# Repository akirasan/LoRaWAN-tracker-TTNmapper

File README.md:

# LoRaWAN-tracker-TTNmapper
Tracker basado en Arduino Mini Pro + GPS + RFM95W (LoRa)
Podéis encontrar toda la info del proyecto en http://akirasan.net/nodo-de-mapeo-ttnmapper-arduino-gps-lorawan

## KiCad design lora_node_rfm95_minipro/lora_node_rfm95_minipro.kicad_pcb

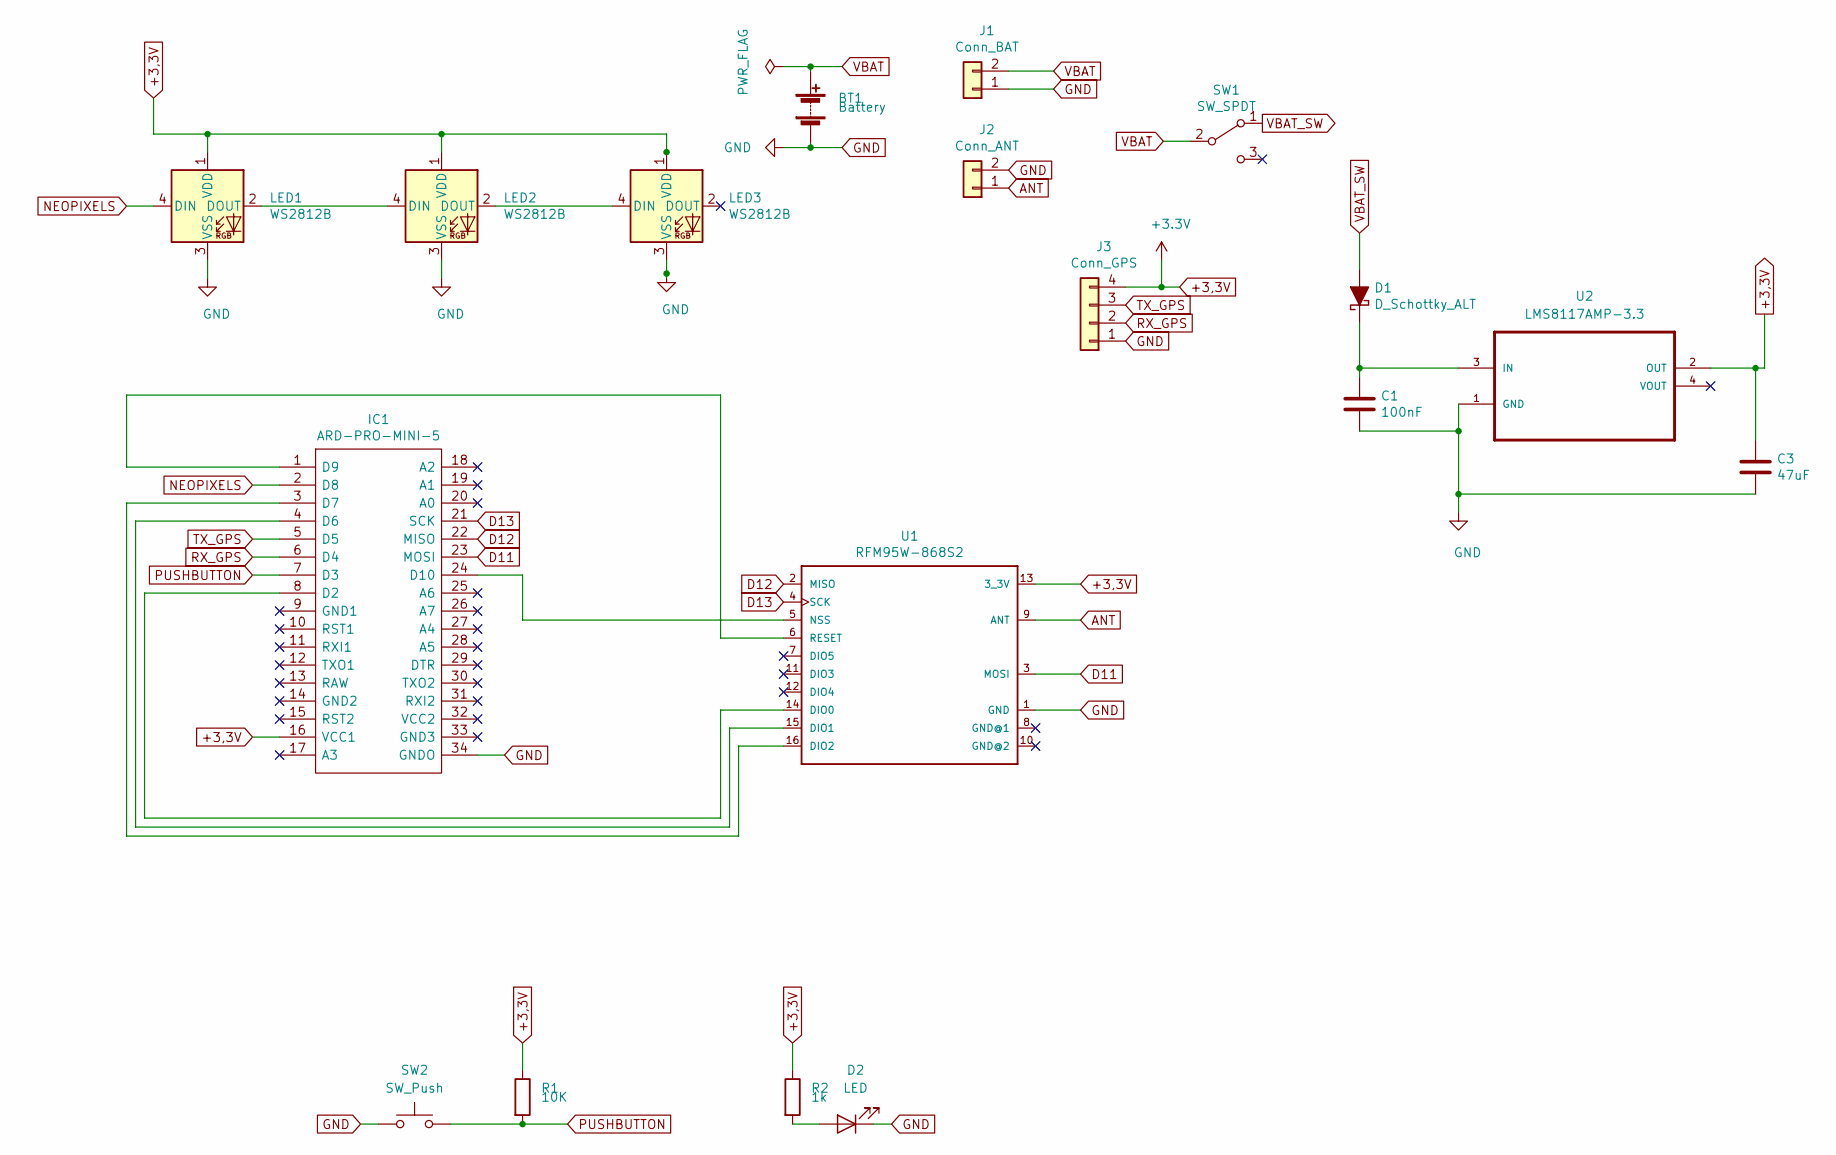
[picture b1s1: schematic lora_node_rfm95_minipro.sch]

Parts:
BT1: Battery
C1: 100nF; C_0805_2012Metric_Pad1.29x1.40mm_HandSolder
C3: 47uF; C_0805_2012Metric_Pad1.29x1.40mm_HandSolder
D1: D_Schottky_ALT; D_1206_3216Metric_Pad1.22x1.80mm_HandSolder
D2: LED; D_0805_2012Metric_Pad1.12x1.40mm_HandSolder
IC1: ARD-PRO-MINI-5; ARDPROMINI5_SMD; Mouser Part Number 992-ARD-PRO-MINI-5
J1: Conn_BAT; JST_PH_B2B-PH-SM4-TB_1x02-1MP_P2.00mm_Vertical
J2: Conn_ANT; SMA_Molex_73251-1153_EdgeMount_Horizontal
J3: Conn_GPS; GPS_module_SMD
LED1, LED2, LED3: WS2812B; LED_WS2812B_PLCC4_5.0x5.0mm_P3.2mm
R1: 10K; R_0805_2012Metric_Pad1.29x1.40mm_HandSolder
R2: 1k; R_0805_2012Metric_Pad1.29x1.40mm_HandSolder
SW1: SW_SPDT; SW_SPDT_PCM12
SW2: SW_Push; SW_SPST_TL3342
U1: RFM95W-868S2; XCVR_RFM95W-868S2
U2: LMS8117AMP-3.3; SOT230P696X180-4N

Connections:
+3,3V: C3.1, IC1.16 (VCC1), J3.4, LED1.1 (VDD), LED2.1 (VDD), LED3.1 (VDD), R1.1, R2.1, U1.13 (3_3V), U2.2 (OUT)
ANT: J2.1, U1.9 (ANT)
D11: IC1.23 (MOSI), U1.3 (MOSI)
D12: IC1.22 (MISO), U1.2 (MISO)
D13: IC1.21 (SCK), U1.4 (SCK)
GND: BT1.2 (-), C1.2, C3.2, D2.1 (K), IC1.34 (GNDO), J1.1, J2.2, J3.1, LED1.3 (VSS), LED2.3 (VSS), LED3.3 (VSS), SW2.1, U1.1 (GND), U2.1 (GND)
NEOPIXELS: IC1.2 (D8), LED1.4 (DIN)
unnamed: C1.1, D1.1 (K), U2.3 (IN)
unnamed: D2.2 (A), R2.2
unnamed: IC1.1 (D9), U1.6 (RESET)
unnamed: IC1.3 (D7), U1.16 (DIO2)
unnamed: IC1.4 (D6), U1.15 (DIO1)
unnamed: IC1.8 (D2), U1.14 (DIO0)
unnamed: IC1.24 (D10), U1.5 (NSS)
unnamed: LED1.2 (DOUT), LED2.4 (DIN)
unnamed: LED2.2 (DOUT), LED3.4 (DIN)
PUSHBUTTON: IC1.7 (D3), R1.2, SW2.2
RX_GPS: IC1.6 (D4), J3.2
TX_GPS: IC1.5 (D5), J3.3
VBAT: BT1.1 (+), J1.2, SW1.2 (B)
VBAT_SW: D1.2 (A), SW1.1 (A)

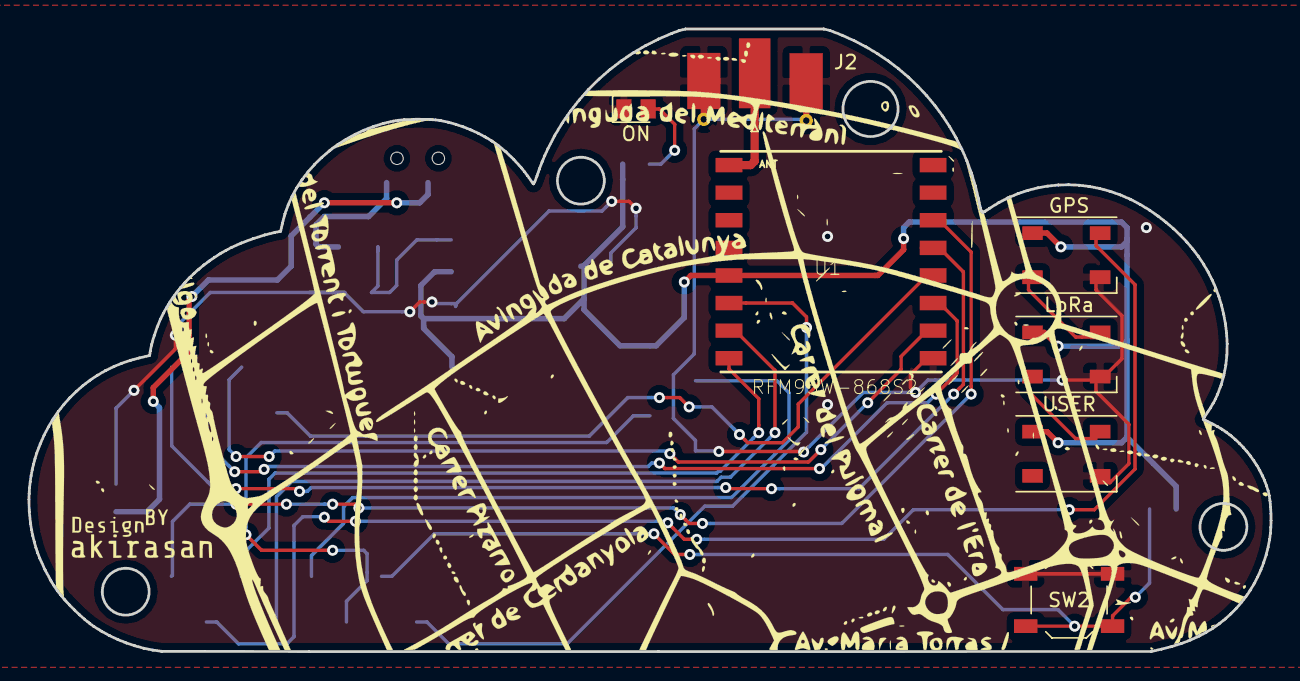
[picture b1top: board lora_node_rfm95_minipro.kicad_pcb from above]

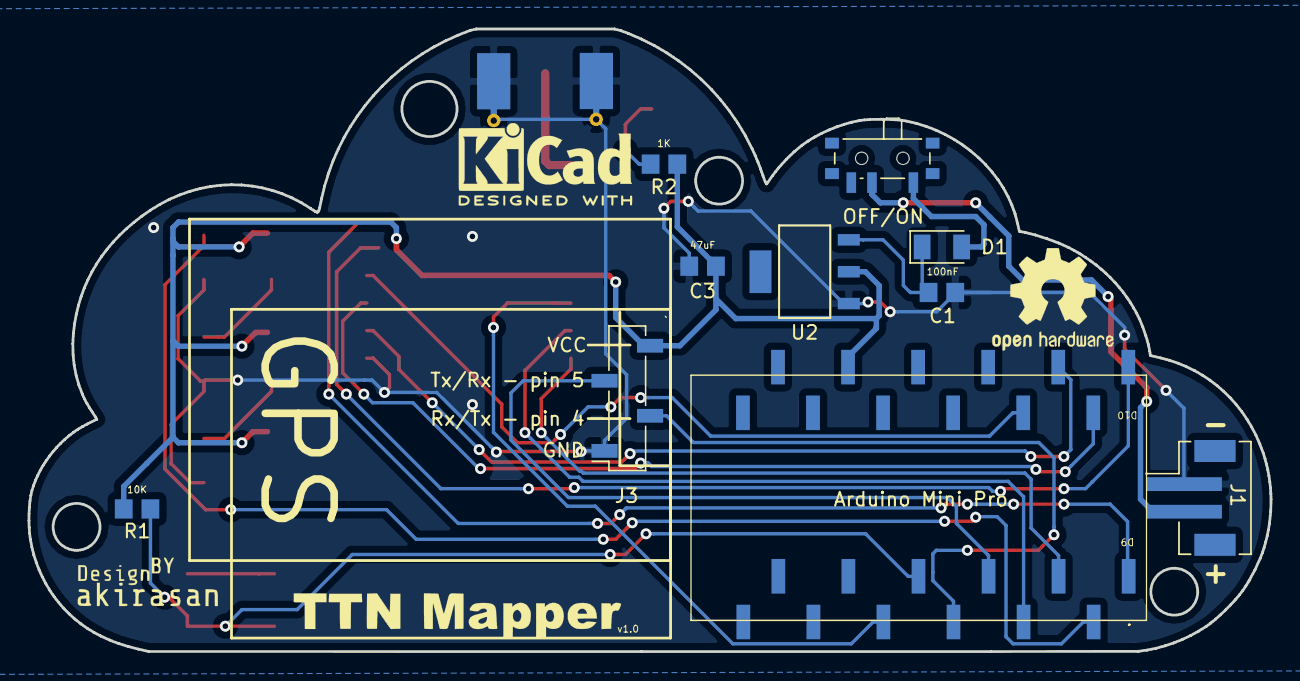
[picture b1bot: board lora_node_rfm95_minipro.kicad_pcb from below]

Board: 2 copper layers, 90.1 x 45.1 mm, 23 parts (12 on the bottom side), 21 nets.

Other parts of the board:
Ref**: Val**; akirasan_logo
Ref**#2: Val**; lorawan_logo_small
Ref**#3: Val**; ttnmapper_logo
Ref**#4: Val**; ttn_cat_logo_small_silks
Ref**#5: Val**; akirasan_logo
Ref**#6: Val**; ttnmapper_logo_small_silks

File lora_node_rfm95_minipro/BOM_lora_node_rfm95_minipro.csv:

"Id";"Designator";"Package";"Quantity";"Designation";"Supplier and ref";
1;"Ref**,Ref**";"akirasan_logo";2;"Val**";;;
2;"J2";"SMA_Molex_73251-1153_EdgeMount_Horizontal";1;"Conn_ANT";;;
3;"U2";"SOT230P696X180-4N";1;"LMS8117AMP-3.3";;;
4;"LED3,LED2,LED1";"LED_WS2812B_PLCC4_5.0x5.0mm_P3.2mm";3;"WS2812B";;;
5;"J3";"GPS_module_SMD";1;"Conn_GPS";;;
6;"IC1";"ARDPROMINI5_SMD";1;"ARD-PRO-MINI-5";;;
7;"C1";"C_0805_2012Metric_Pad1.29x1.40mm_HandSolder";1;"100nF";;;
8;"C3";"C_0805_2012Metric_Pad1.29x1.40mm_HandSolder";1;"47uF";;;
9;"D1";"D_1206_3216Metric_Pad1.22x1.80mm_HandSolder";1;"D_Schottky_ALT";;;
10;"SW1";"SW_SPDT_PCM12";1;"SW_SPDT";;;
11;"SW2";"SW_SPST_TL3342";1;"SW_Push";;;
12;"J1";"JST_PH_B2B-PH-SM4-TB_1x02-1MP_P2.00mm_Vertical";1;"Conn_BAT";;;
13;"U1";"XCVR_RFM95W-868S2";1;"RFM95W-868S2";;;
14;"D2";"D_0805_2012Metric_Pad1.12x1.40mm_HandSolder";1;"LED";;;
15;"R1";"R_0805_2012Metric_Pad1.29x1.40mm_HandSolder";1;"10K";;;
16;"R2";"R_0805_2012Metric_Pad1.29x1.40mm_HandSolder";1;"1K";;;
17;"";"calles_ok";1;"";;;
18;"";"arduino_small_logo";1;"";;;
19;"Ref**";"lorawan_logo_small";1;"Val**";;;
20;"Ref**";"ttnmapper_logo";1;"Val**";;;
21;"Ref**";"ttn_cat_logo_small_silks";1;"Val**";;;
22;"REF**";"KiCad-Logo2_6mm_SilkScreen";1;"KiCad-Logo2_6mm_SilkScreen";;;
23;"REF**";"OSHW-Logo2_9.8x8mm_SilkScreen";1;"OSHW-Logo2_9.8x8mm_SilkScreen";;;
24;"Ref**";"ttnmapper_logo_small_silks";1;"Val**";;;

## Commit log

2019-04-01 PCB TTN
2019-04-01 BOM file
